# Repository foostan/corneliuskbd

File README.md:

# Cornelius Keyboard

There are several version.
- v1: Cornelius, [geekhack](https://geekhack.org/index.php?topic=109741.msg2982321#msg2982321)
- v2: Cornelius Low-profile, [youtube](https://youtu.be/LSguWsNrmjk?si=NGWuKMaY3wJwlkxV)

This is the public repository for Cornelius keyboard series.
<p xmlns:cc="http://creativecommons.org/ns#" xmlns:dct="http://purl.org/dc/terms/"><span property="dct:title">Cornelius Keyboard</span> by <span property="cc:attributionName">foostan</span> is licensed under <a href="http://creativecommons.org/licenses/by-nc-sa/4.0/?ref=chooser-v1" target="_blank" rel="license noopener noreferrer" style="display:inline-block;">CC BY-NC-SA 4.0</a></p>

## v1 Cornelius

## v2 Cornelius Low-profile

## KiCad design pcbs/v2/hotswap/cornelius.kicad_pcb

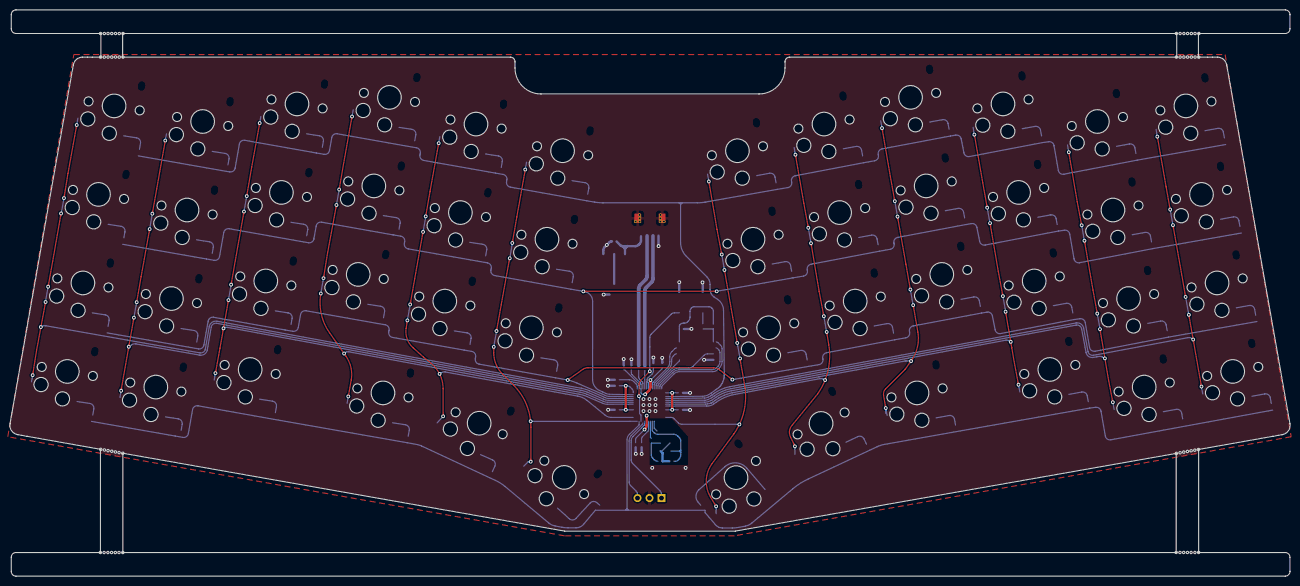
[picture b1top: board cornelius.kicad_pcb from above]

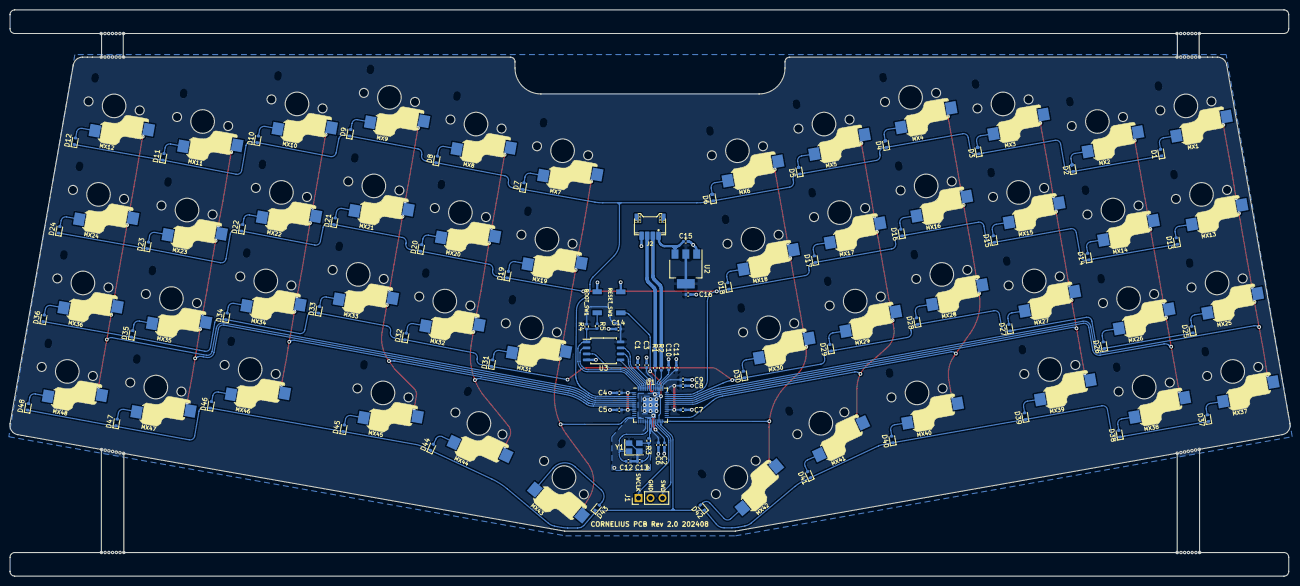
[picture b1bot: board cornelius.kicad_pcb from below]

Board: 2 copper layers, 271.3 x 120.0 mm, 133 parts (125 on the bottom side), 85 nets.

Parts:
B1, B2, B3, B4, B5, B6, B7, B8: BreakAwayTab; Breakaway_Tabs
BOOT_SW1: TS-1088R-02026
C1, C2, C3, C4, C5, C6, C7, C8, C9: 100n; C_0402_1005Metric
C10, C11, C14: 1u; C_0402_1005Metric
C12, C13: 27p; C_0402_1005Metric
C15, C16: 10u; C_0402_1005Metric
D1, D2, D3, D4, D5, D6, D7, D8, D9, D10, D11, D12, D13, D14, D15, D16, D17, D18, D19, D20, D21, D22, D23, D24, D25, D26, D27, D28, D29, D30, D31, D32, D33, D34, D35, D36, D37, D38, D39, D40, D41, D42, D43, D44, D45, D46, D47, D48: SOD-523; D_SOD-523
J1: Conn_01x03; PinHeader_1x03_P2.54mm_Vertical
J2: 78171-0004; Pico-EZmate_PCB_Header
MX1, MX2, MX3, MX4, MX5, MX6, MX7, MX8, MX9, MX10, MX11, MX12, MX13, MX14, MX15, MX16, MX17, MX18, MX19, MX20, MX21, MX22, MX23, MX24, MX25, MX26, MX27, MX28, MX29, MX30, MX31, MX32, MX33, MX34, MX35, MX36, MX37, MX38, MX39, MX40, MX41, MX42, MX43, MX44, MX45, MX46, MX47, MX48: SW_Push; keyswitch_choc12_hotswap_1u
R1, R2: 27; R_0402_1005Metric
R3, R5: 1k; R_0402_1005Metric
R4: 10k; R_0402_1005Metric
RESET_SW1: TS-1088R-02026
U1: RP2040; QFN-56-1EP_7x7mm_P0.4mm_EP3.2x3.2mm
U2: NCP1117-3.3_SOT223; SOT-223-3_TabPin2
U3: W25Q128JVSIQ; SOIC-8_5.23x5.23mm_P1.27mm
Y1: 12MHz 18pF; Crystal_SMD_3225-4Pin_3.2x2.5mm

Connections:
+1V1: C1.1, C2.1, C10.1, U1.23 (DVDD), U1.45 (VREG_VOUT), U1.50 (DVDD)
+3V3: C3.1, C4.1, C5.1, C6.1, C7.1, C8.1, C9.1, C11.1, C14.1, C16.1, R4.2, U1.1 (IOVDD), U1.10 (IOVDD), U1.22 (IOVDD), U1.33 (IOVDD), U1.42 (IOVDD), U1.43 (ADC_AVDD), U1.44 (VREG_IN), U1.48 (USB_VDD), U1.49 (IOVDD), U2.2 (VO), U3.8 (VCC)
+5V: C15.1, J2.1, U2.3 (VI)
/cornelius/D+: J2.3, R1.1
/cornelius/D-: J2.2, R2.2
/cornelius/QSPI_SCLK: U1.52 (QSPI_SCLK), U3.6 (CLK)
/cornelius/QSPI_SD0: U1.53 (QSPI_SD0), U3.5 (DI(IO0))
/cornelius/QSPI_SD1: U1.55 (QSPI_SD1), U3.2 (DO(IO1))
/cornelius/QSPI_SD2: U1.54 (QSPI_SD2), U3.3 (IO2)
/cornelius/QSPI_SD3: U1.51 (QSPI_SD3), U3.7 (IO3)
/cornelius/QSPI_SS: R4.1, R5.2, U1.56 (QSPI_SS), U3.1 (~CS)
/cornelius/SWCLK: J1.1, U1.24 (SWCLK)
/cornelius/SWD: J1.3, U1.25 (SWD)
/cornelius/col0: MX1.1, MX13.1, MX25.1, MX37.1, U1.39 (GPIO27_ADC1)
/cornelius/col1: MX2.1, MX14.1, MX26.1, MX38.1, U1.38 (GPIO26_ADC0)
/cornelius/col2: MX3.1, MX15.1, MX27.1, MX39.1, U1.37 (GPIO25)
/cornelius/col3: MX4.1, MX16.1, MX28.1, MX40.1, U1.36 (GPIO24)
/cornelius/col4: MX5.1, MX17.1, MX29.1, MX41.1, U1.29 (GPIO18)
/cornelius/col5: MX6.1, MX18.1, MX30.1, MX42.1, U1.28 (GPIO17)
/cornelius/col6: MX7.1, MX19.1, MX31.1, MX43.1, U1.14 (GPIO11)
/cornelius/col7: MX8.1, MX20.1, MX32.1, MX44.1, U1.8 (GPIO6)
/cornelius/col8: MX9.1, MX21.1, MX33.1, MX45.1, U1.7 (GPIO5)
/cornelius/col9: MX10.1, MX22.1, MX34.1, MX46.1, U1.6 (GPIO4)
/cornelius/col10: MX11.1, MX23.1, MX35.1, MX47.1, U1.5 (GPIO3)
/cornelius/col11: MX12.1, MX24.1, MX36.1, MX48.1, U1.4 (GPIO2)
/cornelius/row0: D1.1 (K), D2.1 (K), D3.1 (K), D4.1 (K), D5.1 (K), D6.1 (K), D7.1 (K), D8.1 (K), D9.1 (K), D10.1 (K), D11.1 (K), D12.1 (K), U1.3 (GPIO1)
/cornelius/row1: D13.1 (K), D14.1 (K), D15.1 (K), D16.1 (K), D17.1 (K), D18.1 (K), D19.1 (K), D20.1 (K), D21.1 (K), D22.1 (K), D23.1 (K), D24.1 (K), U1.41 (GPIO29_ADC3)
/cornelius/row2: D25.1 (K), D26.1 (K), D27.1 (K), D28.1 (K), D29.1 (K), D30.1 (K), D31.1 (K), D32.1 (K), D33.1 (K), D34.1 (K), D35.1 (K), D36.1 (K), U1.40 (GPIO28_ADC2)
/cornelius/row3: D37.1 (K), D38.1 (K), D39.1 (K), D40.1 (K), D41.1 (K), D42.1 (K), D43.1 (K), D44.1 (K), D45.1 (K), D46.1 (K), D47.1 (K), D48.1 (K), U1.27 (GPIO16)
GND: BOOT_SW1.1, C1.2, C2.2, C3.2, C4.2, C5.2, C6.2, C7.2, C8.2, C9.2, C10.2, C11.2, C12.2, C13.2, C14.2, C15.2, C16.2, J1.2, J2.4, J2.MP (MountPin), RESET_SW1.1, U1.19 (TESTEN), U1.57 (GND), U2.1 (GND), U3.4 (GND), Y1.2, Y1.4
unnamed: BOOT_SW1.2, R5.1
unnamed: C13.1, R3.1, Y1.3
unnamed: D1.2 (A), MX1.2
unnamed: D2.2 (A), MX2.2
unnamed: D3.2 (A), MX3.2
unnamed: D4.2 (A), MX4.2
unnamed: D5.2 (A), MX5.2
unnamed: D6.2 (A), MX6.2
unnamed: D7.2 (A), MX7.2
unnamed: D8.2 (A), MX8.2
unnamed: D9.2 (A), MX9.2
unnamed: D10.2 (A), MX10.2
unnamed: D11.2 (A), MX11.2
unnamed: D12.2 (A), MX12.2
unnamed: D13.2 (A), MX13.2
unnamed: D14.2 (A), MX14.2
unnamed: D15.2 (A), MX15.2
unnamed: D16.2 (A), MX16.2
unnamed: D17.2 (A), MX17.2
unnamed: D18.2 (A), MX18.2
unnamed: D19.2 (A), MX19.2
unnamed: D20.2 (A), MX20.2
unnamed: D21.2 (A), MX21.2
unnamed: D22.2 (A), MX22.2
unnamed: D23.2 (A), MX23.2
unnamed: D24.2 (A), MX24.2
unnamed: D25.2 (A), MX25.2
unnamed: D26.2 (A), MX26.2
unnamed: D27.2 (A), MX27.2
unnamed: D28.2 (A), MX28.2
unnamed: D29.2 (A), MX29.2
unnamed: D30.2 (A), MX30.2
unnamed: D31.2 (A), MX31.2
unnamed: D32.2 (A), MX32.2
unnamed: D33.2 (A), MX33.2
unnamed: D34.2 (A), MX34.2
unnamed: D35.2 (A), MX35.2
unnamed: D36.2 (A), MX36.2
unnamed: D37.2 (A), MX37.2
unnamed: D38.2 (A), MX38.2
unnamed: D39.2 (A), MX39.2
unnamed: D40.2 (A), MX40.2
unnamed: D41.2 (A), MX41.2
unnamed: D42.2 (A), MX42.2
unnamed: D43.2 (A), MX43.2
unnamed: D44.2 (A), MX44.2
unnamed: D45.2 (A), MX45.2
unnamed: D46.2 (A), MX46.2
unnamed: D47.2 (A), MX47.2
unnamed: D48.2 (A), MX48.2
unnamed: RESET_SW1.2, U1.26 (RUN)
unnamed: R2.1, U1.46 (USB_DM)
unnamed: R1.2, U1.47 (USB_DP)
unnamed: C12.1, U1.20 (XIN), Y1.1
unnamed: R3.2, U1.21 (XOUT)

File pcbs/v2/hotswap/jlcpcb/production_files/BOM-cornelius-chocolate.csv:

Comment,Designator,Footprint,LCSC
W25Q128JVSIQ,U3,SOIC-8_5.23x5.23mm_P1.27mm,C113767
1k,"R3,R5",R_0402_1005Metric,C11702
NCP1117-3.3_SOT223,U2,SOT-223-3_TabPin2,C146799
100n,"C1,C2,C3,C4,C5,C6,C7,C8,C9",C_0402_1005Metric,C1525
10u,"C15,C16",C_0402_1005Metric,C15525
27p,"C12,C13",C_0402_1005Metric,C1557
RP2040,U1,QFN-56-1EP_7x7mm_P0.4mm_EP3.2x3.2mm,C2040
SOD-523,"D1,D10,D11,D12,D13,D14,D15,D16,D17,D18,D19,D2,D20,D21,D22,D23,D24,D25,D26,D27,D28,D29,D3,D30,D31,D32,D33,D34,D35,D36,D37,D38,D39,D4,D40,D41,D42,D43,D44,D45,D46,D47,D48,D5,D6,D7,D8,D9",D_SOD-523,C232841
10k,R4,R_0402_1005Metric,C25744
27,"R1,R2",R_0402_1005Metric,C2909343
TS-1088R-02026,"BOOT_SW1,RESET_SW1",TS-1088R-02026,C455280
1u,"C10,C11,C14",C_0402_1005Metric,C52923
SW_Push,"MX1,MX10,MX11,MX12,MX13,MX14,MX15,MX16,MX17,MX18,MX19,MX2,MX20,MX21,MX22,MX23,MX24,MX25,MX26,MX27,MX28,MX29,MX3,MX30,MX31,MX32,MX33,MX34,MX35,MX36,MX37,MX38,MX39,MX4,MX40,MX41,MX42,MX43,MX44,MX45,MX46,MX47,MX48,MX5,MX6,MX7,MX8,MX9",keyswitch_choc12_hotswap_1u,C5333465
78171-0004,J2,Pico-EZmate_PCB_Header,C588524
12MHz 18pF,Y1,Crystal_SMD_3225-4Pin_3.2x2.5mm,C91749

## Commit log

2021-06-26 Add buildguide files
2021-06-26 Rename
2021-07-12 Add text and screen shots
2021-07-13 Update buildguide for ja
2021-07-13 Remove unnecessary methods
2021-07-13 Update buildguide for en
2021-07-13 Update how to deal it
2021-07-13 Update images and some comments
2021-07-13 Fix typo (form → foam)
2021-07-16 Update docs for how to fix
2021-07-16 Update some comments
2021-07-17 Add plate and foam data
2021-08-08 Add mock-up-body
2023-11-12 Change LICENSE to BY-NC-SA 4.0
2023-11-12 Add .gitignore
2023-11-12 Add pcb files
2023-11-12 Add makefile
2023-11-12 Squashed 'pcb/kbd/' content from commit 51de1d9
    git-subtree-dir: pcb/kbd
    git-subtree-split: 51de1d90c9d909ca0fc34986691014b41b4bf398
2023-11-12 Squashed 'pcb/kbd/' changes from 51de1d9..d3325a6
    d3325a6 Update
    e87945a Update footprints for crkbd4
    git-subtree-dir: pcb/kbd
    git-subtree-split: d3325a6fa2d7ededd6e092e9450e59ab983efbb4
2023-11-12 Add hotswap pcb
2023-11-12 Remove kbd
2023-11-12 Squashed 'pcb/kbd/' content from commit d3325a6
    git-subtree-dir: pcb/kbd
    git-subtree-split: d3325a6fa2d7ededd6e092e9450e59ab983efbb4
2023-11-12 Update jlcpcb files
2023-11-12 Squashed 'pcb/kbd/' changes from d3325a6..e24354d
    e24354d Fix choc footprints
    git-subtree-dir: pcb/kbd
    git-subtree-split: e24354ddaec81db4c7b912fca939025e305833db
2023-11-12 Add solder pcb
2023-11-12 Remove common/kbd
2023-11-12 Squashed 'pcb/common/kbd/' content from commit 79230bb
    git-subtree-dir: pcb/common/kbd
    git-subtree-split: 79230bbdc12f02f9bfed5b3f6131fb8971f0ae00
2023-11-12 Update solder pcb
2023-11-15 Update zd
2023-11-15 Fix pass capacitor
2023-11-15 Cleanup directories
2023-11-15 Update Makefile
2023-11-15 Change plate data from dxf to svg
2023-11-21 Fix path
2024-01-04 Add a process to flash the newest firmaware
2024-01-04 Add /n
2024-08-31 Separate to v1 directories
2024-08-31 Fix paths
2024-08-31 Add v2 files
2024-08-31 Genarate jlcfiles
2024-08-31 Remove kbd libs
2024-08-31 Squashed 'pcbs/v1/common/kbd/' content from commit c53bf51
    git-subtree-dir: pcbs/v1/common/kbd
    git-subtree-split: c53bf519ed9e0a498869ab56d44385f89ec54b36
2024-08-31 Squashed 'pcbs/v2/common/kbd/' content from commit c53bf51
    git-subtree-dir: pcbs/v2/common/kbd
    git-subtree-split: c53bf519ed9e0a498869ab56d44385f89ec54b36
2024-08-31 Add build guilde of v2
2024-12-13 Update foams for v2
